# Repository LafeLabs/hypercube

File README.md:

# Geometron Hypercube

## Trash Magic

 Trash Magic self-replicating media which propagates the means of building a civilization entirely from trash and things we can grow.  

## What is the Hypercube?

The Geometron Hypercube is two things: The set of all of the 4 inch cubes we make from cardboard trash which are the basis of our physical technology and a geometric language based on the fundamental symmetries of the Universe.  We construct both of these things in order to make it easier to build Trash Magic, using the power of geometry to build things which can be easily replicated and which can build a very wide range of useful objects.  The word "hypercube" here is used to represent generalizations of the cube into higher dimensions in a broad sense.  We take this to mean a set containing many different cubes of many different kinds.

## The Cardboard Hypercube

The cube is 4 inches on a side and can be used for:

 - pencil/rulers/pens/brushes/shapes box
 - marketing display
 - card box for Geometron Trash Magic Cards
 - mushroom farms
 - worm farms
 - [link to oyster mushroom cardboard farming](https://grocycle.com/grow-mushrooms-on-cardboard/)
 - [buy worms to farm in compost bins](https://unclejimswormfarm.com/order-stuff/composting-worms/)
 - tiny compost piles
 - plants, seedlings
 - dice
 - parts bins
 - motion sense control pyramids
 - motor fixture
 - geometron icon printer tower
 - large collaborative art structures
 - lamps

[tiktok of hand cut cube without a laser](https://www.tiktok.com/t/ZTR8AFMJp)

To make one cube, cut out 12 of these from corrugated cardboard, stack them into four panels 3 layers thick and glue them using Elmer's glue:

.svg file for laser cutter:

Now cut out 3 of the bottom pieces, and stack them into a fifth glued panel. 

.svg file for laser cutter:

Assemble the sides into the base as shown:

Cut out 4 inch squares, print on them, glue them to the panels, and hold it all together with rubber bands:

Every cube we produce in the Trash Robot Network is part of the Geometron Hypercube.  Therefore to grow the Hypercube, we produce and distribute as many cubes as we can, and always evolve the cubes to make them better over time and to solve specific problems to bring us closer to Trash Magic.

## Action Geometry Tools: Rulers and Shapes

To make geometric constructions out of cardboard trash, we use the tools of Action Geometry, which are created with the Geometron Language.  These include the ruler, which we cut from 0.2 or 0.25 inch thick neon green acrylic and the shape sets which we cut from 0.1 or 0.125 inch thick neon green acrylic.  

### Geometron Ruler

The Geometron Ruler is one inch by six inches. One side has tenths and the other halves, quarters and eights. The highest quality rulers are made from quarter inch neon green acrylic with a laser cutter.  Any ruler can be used to make more rulers.  Cereal box cardboard is a good material.  Find a maker space or individual with a laser cutter.  Dig through the waste bin to find extra acrylic.  Place the outlines and etch and make rulers.  Give them away and spread the word of Geometron, Trash Magic, Trash Robot and so on.  Also you can use [Ponoko.com](https://www.ponoko.com/) to get large numbers of rulers made and can sell those if you so choose.  

Using Ponoko.com is only cost effective if you have a budget of over 1000 dollars, then the cost per ruler can drop to about a dollar and a half.  Also, Ponoko only has eighth inch acrylic and quarter inch is the nicest.  For best results, go find 0.2 inch or quarter inch neon green acrylic somewhere, find a laser cutter and print these out yourself.  All the files for this are below.  

This is some 6 inch rulers from both green and yellow acrylic and a 15 cm metric ruler.

Ruler Outline SVG file:

Ruler Etch pattern PNG file:  

Ruler 2 color SVG file for Ponoko.com:

Set of 8 rulers in one SVG file for Ponoko.com:

Centimeters PNG file for etch.  Print out with 15 centimeter width and 2 cm height:

centimeters Ruler Outline SVG file, line up with etch and make 15x2 cm:

One ruler with etch and cut in different layers:

Set of 8 cm rulers in one SVG file for Ponoko.com:

## Shapes

These shapes are used for constructions based on fundamental symmetries: fourfold, eightfold, threefold, fivefold, and sixfold.  For best results, we cut them out from eight inch neon green acrylic with a laser cutter.

.svg file for use in laser cutter.  Each shape has side of 3 inches, so this is a 6 inch wide file:

These can all also be constructed using the tools of classical geometry(compass and ruler) or a ruler and a protractor.  So they can be made by hand and cut out from cardboard or paper trash if no laser or acrylic is available.

##  Geometron Icon Printer
 
 - [link to program the Arduino UNO in the Printer Robot](arduino.html)
 - [link to global image feed](globalimagefeed.html)
 - [link to image aligner](alignimage.html)
 - [link to icon tracer](traceicon.html)
 - [link to icon set](iconset.html)

## Things to buy for the electronics kit:

 - [3 motor controller boards from Pololu(10x3=$30)](https://www.pololu.com/product/2966)
 - [Custom printed circuit board to connect Arduino to controllers and connectors($2/ea in lots of 20 with shipping)](https://www.pcbway.com/project/shareproject/Trash_Robot_main__brain__board.html)
 - [straight 0.1 inch headers from Digikey(buy about 2 per kit at about 60 cents each)](https://www.digikey.com/en/products/detail/chip-quik-inc/HDR100IMP40M-G-V-TH/5978197)
 - [Ribbon cable from Digikey(about $8 for about 6 kits worth for about $2/kit rounding up )](https://www.digikey.com/en/products/detail/assmann-wsw-components/AWG28-20-F-1-300-R/2391636)
 - [8 buttons for controller from Digikey(about $1 for all 8)](https://www.digikey.com/en/products/detail/te-connectivity-alcoswitch-switches/FSM2JRT/529664)
 - [Cables from Digikey to connect stepper motors in DVD drive stages to circuit board(about $10 for 3 of them)](https://www.digikey.com/en/products/detail/molex/2177971043/14637940)
 - [Arduino Uno from Sparkfun($25, some off brand UNOs have power supply problems for this application, test any new board to see if it stalls out)](https://www.sparkfun.com/products/11021)
 - [9 pin socket headers](https://www.digikey.com/en/products/detail/samtec-inc/SSQ-109-03-T-S/1111949)

## Kit Photo:

## Control Panel Geometry

## Assembled Electronics Kit Photo

##  DVD drive cables

[Cables from Digikey to connect stepper motors in DVD drive stages to circuit board(about $10 for 3 of them)](https://www.digikey.com/en/products/detail/molex/2177971043/14637940)

## Z axis Stage Assembly

## X and Y axis stage assemblies

## Sproing

Two each of a 0.5 inch by 4 inch thin HDPE sheet and two 0.5 inches by 3 inches thick stiffer plastic.  All held on by rubber bands as shown, as well as attached to the Z stage.

## Full assembly

[link to icon design scroll](scrolls/icons)

[link back to home scroll](scrolls/home)

## Arduino Shields

 - hole in the bottom of box image with ruler position
 - eagle files
 - link to buy 
 - list of components
 - digikey shopping cart
 - photo of assembly for neopixel
 - photo of assembly for sense pyramid
 - sense pyramid photo
 - sense pyramid triangles
 - link to neopixel code
 - link to github repo
 - link to pyramids 3 sense code
 - photo of rotor setup

## Card Magic

## Bags and Flags

## Hypercube Cart

 - 200 W solar panel
 - lead acid battery power plant with weather protection
 - 12x8 inch laser cutter with 40 or 50 W CO2 laser, converted to geometron operation
 - independent suspension and weather protection for laser cutter
 - power output: 12 volt regulated, USB chargers, inverter for AC wall power
 - power input: solar panels, wall charge, car charge, bicycle charger, wind, water
 - Raspberry Pi Geometron Server with the whole system from [https://github.com/LafeLabs/hypercube](https://github.com/LafeLabs/hypercube)
 - setup for pi with small screen, projector, portable screen for projector, geometron keyboard(s), mouse, USB thumb drive to get files onto pi crust
 - neopixel strips lighting up the whole system
 - arduino shields for neopixel, pyramids, motors, robots, etc, arduino setups, boards
 - cube stack: lots of cubes of all kinds: card boxes, art boxes, parts boxes, planters with plants, fungi, compost, empties, parts to make more
 - fully set up geometron icon printer to print on cards, cubes, and trash
 - hanging green wall of plants
 - tarp, awning for getting out of rain 
 - folding chair to sit under awning
 - neon green acrylic shape sets and rulers
 - router to connect to mesh network or cell network and make a wifi hotspot

## Geometron: A Universal Language of Geometric Construction

Geometron is a language for creating geometric constructions using these symmetries.  We aim to build the most powerful possible interface between the human mind and the physical world.  To do this we build geometric actions based on the fundamental symmetries of the Universe.  We represent those actions using symbols we construct using that same set of actions.  We describe each of the geometric actions using a human language we understand, with phrases like "draw a unit circle", while also creating symbols which are used in the language to express itself.  

Geometron is constructed independent of any one physical technology to implement it, or any one set of symbols.  It is a means of creating symbolic geometric languages.  The Geometron Hypercube elements which make up the language are an arrangement of geometric actions into cubes.  One cube contains all the actions which are not explicitly symbols, and the other cube represents all the symbols for the actions in the action cube.  Each cube is broken up into a crystal of 8 by 8 by 8 cubes.  Each of those cubes contains a sequence of cube addresses, which are geometric actions.  Thus the Geometron Hypercube is a model for constructing geometric and symbolic languages which we can build up by hand using pencil and paper, and then implement in any computer language relatively quickly.  

A Geometron Glyph is a sequence of these geometric actions which are represented by addresses in the Hypercube.  These glyphs are abstractions which can be expressed as sequences of symbols in any format(a browser, a pen and paper, a printer or plotter) but which can apply to ***any kind of physical construction***.  This might include movements of motors in robotic machines which carry out automation of production, like laser cutters, electron beam writing tools, milling tools or 3d printer heads.  Or it might include lighting up pixels on a screen or deflecting the beam of a cathode ray tube.  

Addresses in the Hypercube all begin with "0" to indicate that they are base 8(digits are all between 0 and 7).  All addresses in the symbol cube have a "1" added.  The Action cube is divided by types of operation into tablets, which are each arrays of 8x8 = 64 actions which can be arranged in a square on a chess board. The planar operations which are used to construct symbols on computers are all in the range from 0300 to 0377(with matching symbols at 01300 to 01377).  The actions in the range from 0200 to 0277(with matching symbols at 01200 to 01277) are all sequences of either planar actions in the 03xy range or other actions in the 02xy range.  Thus we can build up complex structures which call other sub-structures.  This is of critical value for design of technology, as we can create complex systems of systems built up from very simple components in a fractal way.  Addresses in the range from 040 to 0176 correspond to the ASCII codes for the characters which can be printed and have a symbol on standard US keyboards.  Fonts in English are stored as sequences of actions in the range from 01040 to 01176.  The contents of each of the ASCII addresses are actions which are triggered when that key is pressed.  This mapping is what is represented physically in the custom painted Geometron keyboards we build.  

### Geometron Keyboards

We assign keys on physical keyboards to symbols which represent actions in order to make it easier to interact with Geometron on a keyboard.  We make these with paint pens, pain brushes, nail polish, stickers, or any other means of decorating keyboards as follows:

These are edited on a Geometron server using the keyboard editing page linked from the main symbol editor.

### Shape Sets

We can use Geometron to create symbolic languages made up of shapes which can be called using their own symbols.  These can be used to create things like the Action Geometry shapes, electronic schematic diagrams, logic gates, chemical diagrams, architectural diagrams, illustrations, and really any kind of symbolic language including for technology design like circuit layout for fabrication.

Some examples of constructions using shape sets

## Fonts

Fonts correspond to the addresses in the symbol cube which map to the key actions in the action cube. I.e. the address is the ASCII value plus 01000 base 8.

Dot Matrix Font:

Laser cut font:

Katakana dot matrix font:

## Symmetries of the Universe

Symmetries are properties of things which remain the same under geometric transformation.  The Universe as we find it displays certain symmetries again and again in both the living and non living world.  Perhaps the most fundamental of these are crystal lattices, where movement in certain directions by certain distances leads to a repeating of patterns.  Perhaps the next most common symmetries we see in Nature are those of certain special rotations: bilateral symmetry, trilateral symmetry, fourfold, fivefold, sixfold, eightfold, tenfold, and twelvefold.  

Each of these special rotational symmetries has certain scales which are built into them.  When we work with squares and octagons, we find the square root of two and two coming up again and again in 45 degree angle constructions.  When we work with hexagons and equilateral triangles, we get scales by the square root of three, three, and two.  And finally anything with fivefold symmetry has the Golden Ratio built into its construction.  

Movement by one unit, just moving from point to point:

Repeated movements can create crystal lattices, like the checkerboard pattern:

A circle is totally symmetric around rotations:

Bilateral symmetry is particularly common in living things:

Threefold symmetry:

Fourfold symmetry

Fivefold symmetry:

Sixfold symmetry:

Fractal based on triangles:

Fractal based on squares:

Fractal based on hexagons:

Fractal based on hexagons:

Symmetry in Nature:

## Server

The server runs the PI CRUST media network which hosts articles, books, videos, music, podcasts and web pages on local servers over local networks.  We can share books on any format, but there is a native book format for the system called the Pibrary format which is collections of "scrolls" in Markdown format. "Maps" are a sort of generalized meme, layers of images, text and symbols arranged geometrically and with hyperlinks both to other web pages and to other maps on the server.  Maps and Scrolls together can be used to create any kind of static web content we want, and are used for both private web content and for public pages to lead people to the physical media nodes. 

Servers run on a zero security model where there is no private data, no users, no encryption, no property and no commerce or money of any kind.  The *only* information ever put on any server ever is that which we aim to freely share as widely as possible, primarily the means of replication of our system the Hypercube and associated Trash Magic. 

### Install on Pi

Raspberry Pi is now impossible to buy.  Find them donated from someone. Most people who have them don't use them or used them once and stopped due to lack of interest/time/need. Ask around!  Someone will be able to donate a Pi, keyboard, mouse, screen, power supply and whatever other random things you need to get set up.

Get a SD card with 8 GB or more storage and a SD card USB reader

Download and install, then use the Raspberry Pi Imager:

[https://www.raspberrypi.org/software/](https://www.raspberrypi.org/software/)

Turn on the pi click through all the things, put it on the wifi network.

## Install Apache and PHP so that geometron can run

Open a command prompt(black link on menu bar) and type:

```
sudo apt update
sudo apt install apache2 -y
sudo apt install php libapache2-mod-php -y
```

## Install hypercube with this document for self-documentation and replication

```
cd /var/www/html
sudo rm index.html
sudo curl -o replicator.php https://raw.githubusercontent.com/LafeLabs/hypercube/main/php/replicator.txt
cd ..
sudo chmod -R 0777 *
cd html
php replicator.php
sudo chmod -R 0777 *
```

Check the IP address by hovering over the wifi icon, put that into the browser on another machine on the same local wifi network to see and edit the server.  Or open a browser on the pi and point it to [http://localhost](http://localhost)

## Set up to have names for other servers

edit hosts file to have the IP address of the other servers and then the name you want to use, copying the format in the existing file.

```
sudo nano /etc/hosts
```
edit, and use control-x and say "yes" to save changes.

## connect pi to outside internet over router

Look up "set up port forwarding raspberry pi" and follow instructions to log onto your router and forward port 80 to the raspberry pi.  Use [whatismyipaddress.com](https://whatismyipaddress.com/) to get your global IP address.  Now your home Raspberry pi server will be visible on that IP address.  Take that address and make it a link on the remote raspberry pi terminal as well as a QR code on both.   

edit the /etc/hosts file on the remote pi terminal so that home/ and remote/ point to home pi server either on the local network or on the public network.  So "home" will point to the local IP address on the wifi and "remote" will point to the global IP address of the home raspberry pi server(which everyone can see).  

[link to pi my life up](https://pimylifeup.com/raspberry-pi-port-forwarding/)

[link to setting up basic website with pi with external connection](http://unixetc.co.uk/2013/09/21/create-a-basic-website-on-a-raspberry-pi/)

## Install Arduino

the short but not as good way:

```
sudo apt-get install arduino
```

this installs a old version which is missing some features, namely the serial plotter.  following more complicated instructions leads to non-working version which is impossible to uninstall.

how to do the tar ball thing to get a later version of arduino which has the plotting

[https://www.raspberrypi-spy.co.uk/2020/12/install-arduino-ide-on-raspberry-pi/](https://www.raspberrypi-spy.co.uk/2020/12/install-arduino-ide-on-raspberry-pi/)

go get the Arduino software at:

[https://www.arduino.cc/en/software](https://www.arduino.cc/en/software)

and download "Linux ARM 32 bits".

Open a terminal and go to the home directory:

```
cd ~
```

Go to downloads folder:
```
cd Downloads
```
list the files with 
```
ls
```
See the name of an archive with a name like "arduino-####-linuxarm.tar.xz", where #### is a version number.

extract with 
```
tar -xf arduino-####-linuxarm.tar.xz
```

move the extracted information to opt directory(directory for package installation)

```
sudo mv arduino-#### /opt
```

then run the install script:
```
sudo /opt/arduino-####/install.sh
```

## Add python that we need for doing science

[https://matplotlib.org/](https://matplotlib.org/)

matplotlib install:

```
sudo apt install python3-matplotlib
```

[https://matplotlib.org/](https://matplotlib.org/)

[https://www.instructables.com/Jupyter-Notebook-on-Raspberry-Pi/](https://www.instructables.com/Jupyter-Notebook-on-Raspberry-Pi/)

```
sudo apt-get update
sudo apt-get install python3-scipy
sudo pip3 install --upgrade pip
reboot
sudo pip3 install jupyter
```

### Install on Windows or Mac

First, install XAMPP, a free open source web server for all platforms.  [Download from www.apachefriends.org](https://www.apachefriends.org/index.html).  Click on windows to download, and click through to install everything.

After you download and install it, run it and start Apache.  You should see a control panel like this:

Click on "Explorer" to get access to where the files are.  From the main directory called xamp, you want the sub-directory "htdocs".  Open this, delete the index.php file, and create a new file called replicator.php which you copy and paste the replicator at [php/replicator.txt](php/replicator.txt) into, and save.  

Point a web browser on the same computer to [http://localhost/](http://localhost), then click on replicator.php.  This should replicate the whole system into the directory.  When this is done, click the link to go to the main page.  

### Install on Android

To run a Geometron Server on an Android, we will install the commercial software ksweb pro.

[link to play store to install ksweb](https://www.google.com/url?sa=t&rct=j&q=&esrc=s&source=web&cd=&cad=rja&uact=8&ved=2ahUKEwiLrtjPw6fxAhUQu54KHWkyAjIQFjAAegQIBRAD&url=https%3A%2F%2Fplay.google.com%2Fstore%2Fapps%2Fdetails%3Fid%3Dru.kslabs.ksweb%26hl%3Den_US%26gl%3DUS&usg=AOvVaw2ChVP4ojXIuGxVe-JjtEV3)

[https://www.kslabs.ru/](https://www.kslabs.ru/)

Install KSWEB on the Android, and turn it on.  Get the paid version. It is worth it, there are lots of broken web servers out there or ones with crappy features and tons of ads.  This is critical infrastructure for Geometron and it's worth supporting the developer of this useful tool.  Be sure PHP is also turned on.  

This is what it looks like when it is on:

Use the Editor built into the system to create a new file called replicator.php in the directory htdocs on the sd card as shown above, and to copy/paste into that the file in [php/replicator.txt](php/replicator.txt).  Save that, and delete index.php. Point a browser to the address [http://localhost:8080](http://localhost:8080).  Click on replicator.php and wait for the system to copy.  Sometimes it might time out, try it again.  When the system has replicated, make sure your phone is on a local wifi network, and turn the server off and on again, and you will get an IP address for the phone which is shown in the app.  The link for any other machine on the network other than the phone is the IP address followed by colon and then "8080".  E.g. http://192.168.0.19:8080/.  Share this link via email, text message, and links on other servers so that anyone on your network can see your server and edit it.  

### Replicate the Github using localhost

 - install PHP on your machine
 - create a new github repository on a CC0 PUBLIC DOMAIN license and clone it on your machine
 - copy the file [php/replicator.txt](php/replicator.txt) into a file called replicator.php in the new repo directory
 - run `php replicator.php` on your machine, wait for all the code to copy
 - push all that code up to your github repo
 - in the same directory, type `sudo php -S localhost:80`
 - go to [http://localhost](http://localhost) and you should get back to this screen, edit all elements of the system
 - use [editor.php](editor.php) to edit the file php/replicator.txt so that the two urls are the global url for *your* repo for both dna and replicator
 - after you've edited the code, click [text2php.php](text2php.php) to convert that to php
 - push your code to your github repo
 - use the new replicator code on your github repo to replicate out that instance to all other servers(linux, windows, mac, android) and forks
 - when you figure this out, make youtube videos showing other people how to copy the whole system 

## Scroll Sets

## Map Sets

## Pi Crust

## Voxel

 - scroll sets
 - map sets 
 - pi crust 
 - qr code
 - [cube voxel AR memes](voxel.html)

## Trash Robot Bags, Flags and Rags

 - photo of shirts and pants
 - photos of all the bags
 - photos of flags

## Links

 - [copy  trashrobot.html to index.html](copy.php?from=https://raw.githubusercontent.com/LafeLabs/geometronmagic/main/trashrobot.html&to=index.html)
 - [copy latest README.md from github](copy.php?from=https://raw.githubusercontent.com/LafeLabs/geometronmagic/main/README.md&to=README.md)
 - [http://localhost/](http://localhost/)

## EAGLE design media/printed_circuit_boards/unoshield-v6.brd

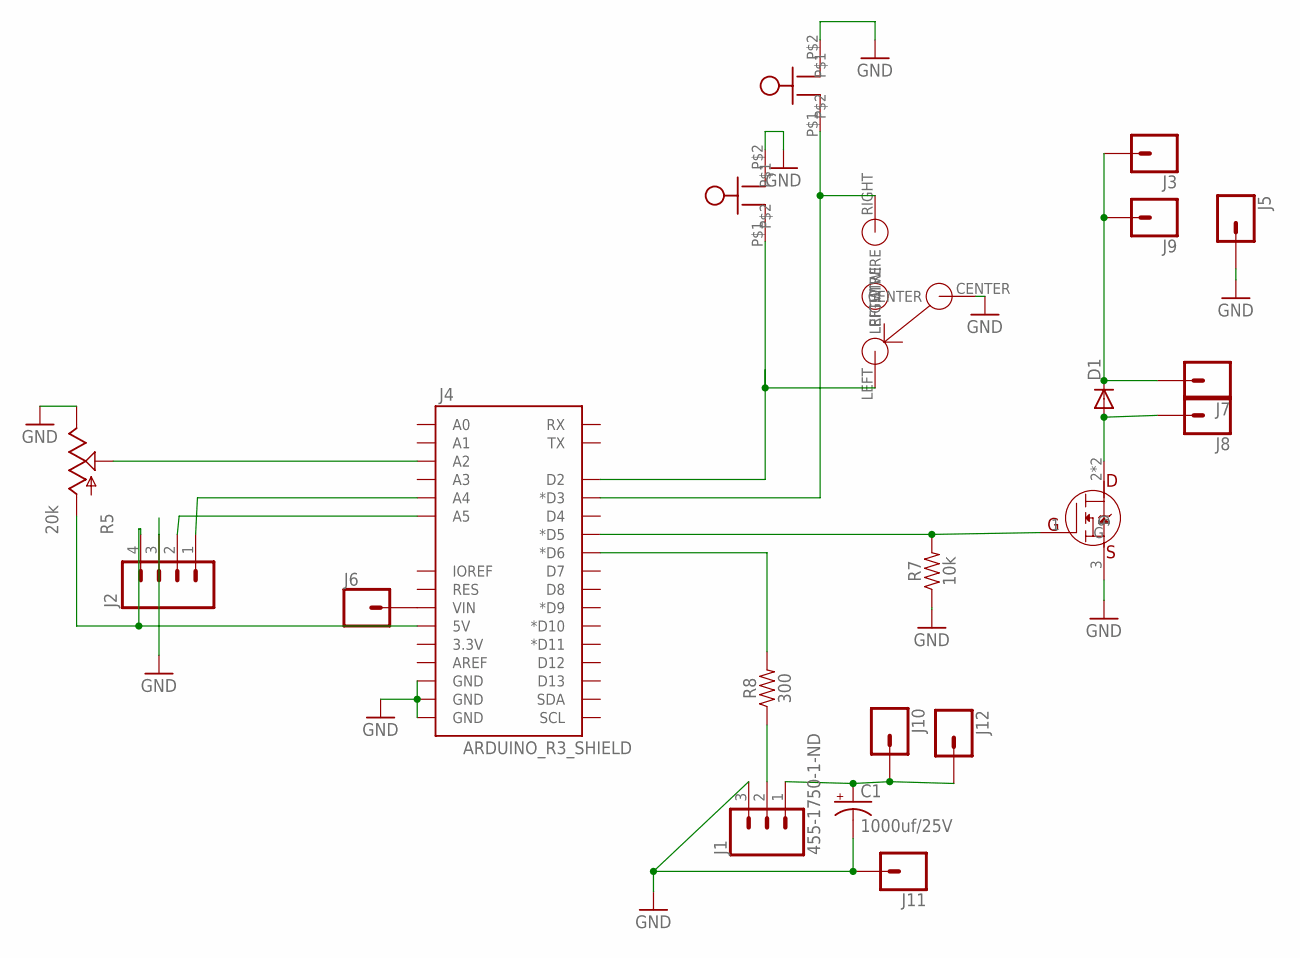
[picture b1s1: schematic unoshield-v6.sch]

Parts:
C1: 1000uf/25V; CPOL-RADIAL-1000UF-25V-KIT
D1: DIODE-DO-214AC; DO-214AC
J1: 455-1750-1-ND; 1X03
J2: M04PTH; 1X04
J3, J5, J7, J8, J10, J11: CONN_01PTH_2MM; 1X01_2MM
J4: ARDUINO_R3_SHIELD; UNO_R3_SHIELD
J6, J9, J12: CONN_01; 1X01
R5: 20k; ALPS_POT_KIT
R7: 10k; AXIAL-0.3
R8: 300; AXIAL-0.3
SW1, SW2: BUTTON
SW3: ON-OFF-ON-360-1013-ND; 360-1013-ND
U$1: IRFL024NPBF; SOT223

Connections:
BUTTON: J4.D3 (*D3), SW2.P$1, SW3.RIGHT (RIGHTWIRE)
CL: J2.2, J4.A5
DA: J2.1, J4.A4
GND: C1.-, J1.3, J2.3, J4.GND@0 (GND), J4.GND@1 (GND), J4.GND@2 (GND), J5.1, J11.1, R5.P$1 (E), R7.P$1 (1), SW1.P$2, SW2.P$2, SW3.CENTER, U$1.3 (S)
unnamed: J4.D5 (*D5), R7.P$2 (2), U$1.1 (G)
unnamed: J4.D6 (*D6), R8.P$2 (2)
unnamed: J4.VIN, J6.1
unnamed: C1.+, J1.1, J10.1, J12.1
unnamed: D1.A, J8.1, U$1.2 (D), U$1.4 (D)
unnamed: J4.D2, SW1.P$1, SW3.LEFT (LEFTWIRE)
unnamed: J1.2, R8.P$1 (1)
unnamed: J4.A2, R5.P$2 (S)
VCC: J2.4, J4.5V, R5.P$3 (A)
VIN: D1.C, J3.1, J7.1, J9.1

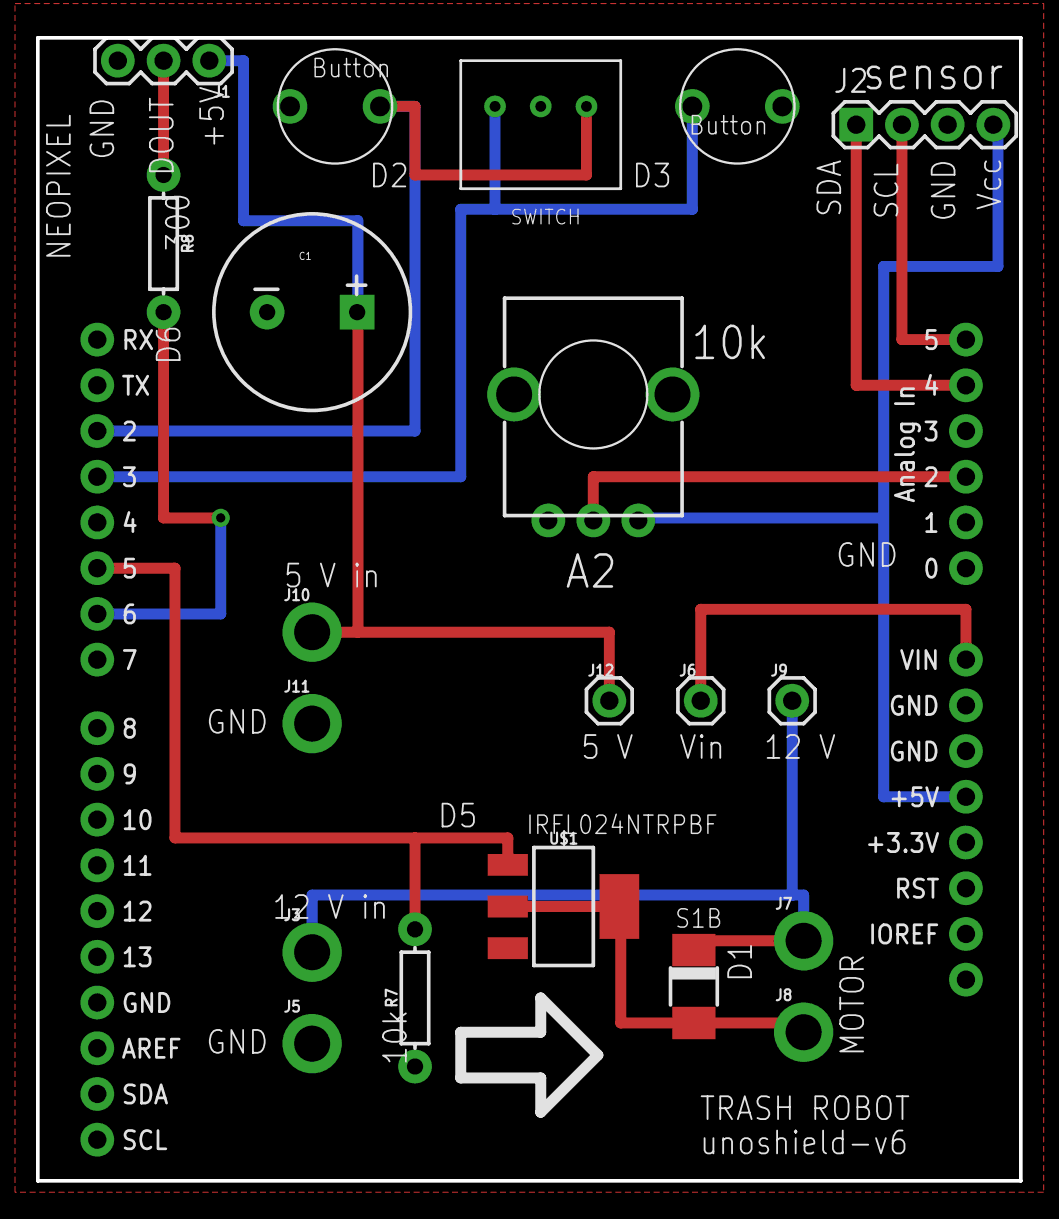
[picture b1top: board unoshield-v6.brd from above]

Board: 2 copper layers, 54.6 x 63.5 mm, 21 parts (0 on the bottom side), 14 nets.

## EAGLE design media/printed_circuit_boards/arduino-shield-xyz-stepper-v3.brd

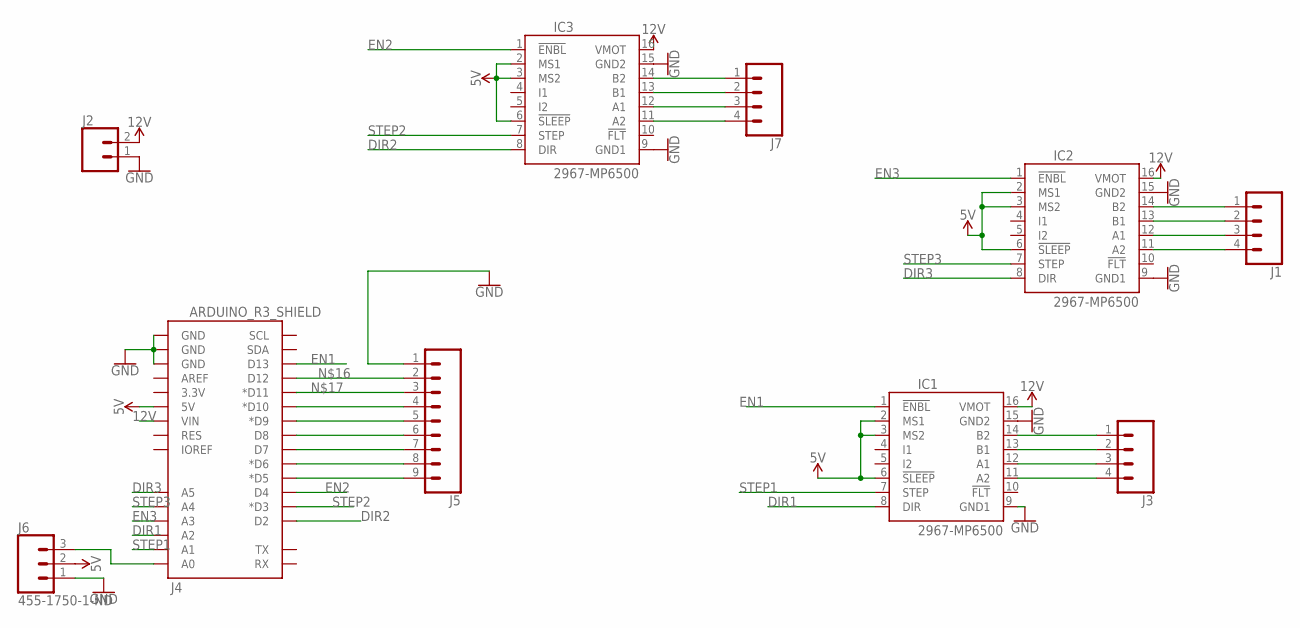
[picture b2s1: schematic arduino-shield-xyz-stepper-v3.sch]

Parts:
IC1, IC2, IC3: 2967-MP6500; MP6500
J1, J3, J7: CONN_04; 1X04
J2: CONN_02; 1X02
J4: ARDUINO_R3_SHIELD; UNO_R3_SHIELD
J5: CONN_09; 1X09
J6: 455-1750-1-ND; 1X03

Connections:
5V: IC1.2 (MS1), IC1.3 (MS2), IC1.6 (!SLEEP), IC2.2 (MS1), IC2.3 (MS2), IC2.6 (!SLEEP), IC3.2 (MS1), IC3.3 (MS2), IC3.6 (!SLEEP), J4.5V, J6.2
12V: IC1.16 (VMOT), IC2.16 (VMOT), IC3.16 (VMOT), J2.2, J4.VIN
DIR1: IC1.8 (DIR), J4.A2
DIR2: IC3.8 (DIR), J4.D2
DIR3: IC2.8 (DIR), J4.A5
EN1: IC1.1 (!ENBL), J4.D13
EN2: IC3.1 (!ENBL), J4.D4
EN3: IC2.1 (!ENBL), J4.A3
GND: IC1.9 (GND1), IC1.15 (GND2), IC2.9 (GND1), IC2.15 (GND2), IC3.9 (GND1), IC3.15 (GND2), J2.1, J4.GND@0 (GND), J4.GND@1 (GND), J4.GND@2 (GND), J5.1, J6.1
unnamed: IC3.14 (B2), J7.1
unnamed: IC3.13 (B1), J7.2
unnamed: IC1.14 (B2), J3.1
unnamed: IC1.13 (B1), J3.2
unnamed: IC1.12 (A1), J3.3
unnamed: IC1.11 (A2), J3.4
unnamed: IC2.14 (B2), J1.1
unnamed: IC2.13 (B1), J1.2
unnamed: IC2.12 (A1), J1.3
unnamed: IC2.11 (A2), J1.4
unnamed: IC3.12 (A1), J7.3
unnamed: IC3.11 (A2), J7.4
unnamed: J4.A0, J6.3
unnamed: J4.D12, J5.2
unnamed: J4.D11 (*D11), J5.3
unnamed: J4.D10 (*D10), J5.4
unnamed: J4.D9 (*D9), J5.5
unnamed: J4.D8, J5.6
unnamed: J4.D7, J5.7
unnamed: J4.D6 (*D6), J5.8
unnamed: J4.D5 (*D5), J5.9
STEP1: IC1.7 (STEP), J4.A1
STEP2: IC3.7 (STEP), J4.D3 (*D3)
STEP3: IC2.7 (STEP), J4.A4

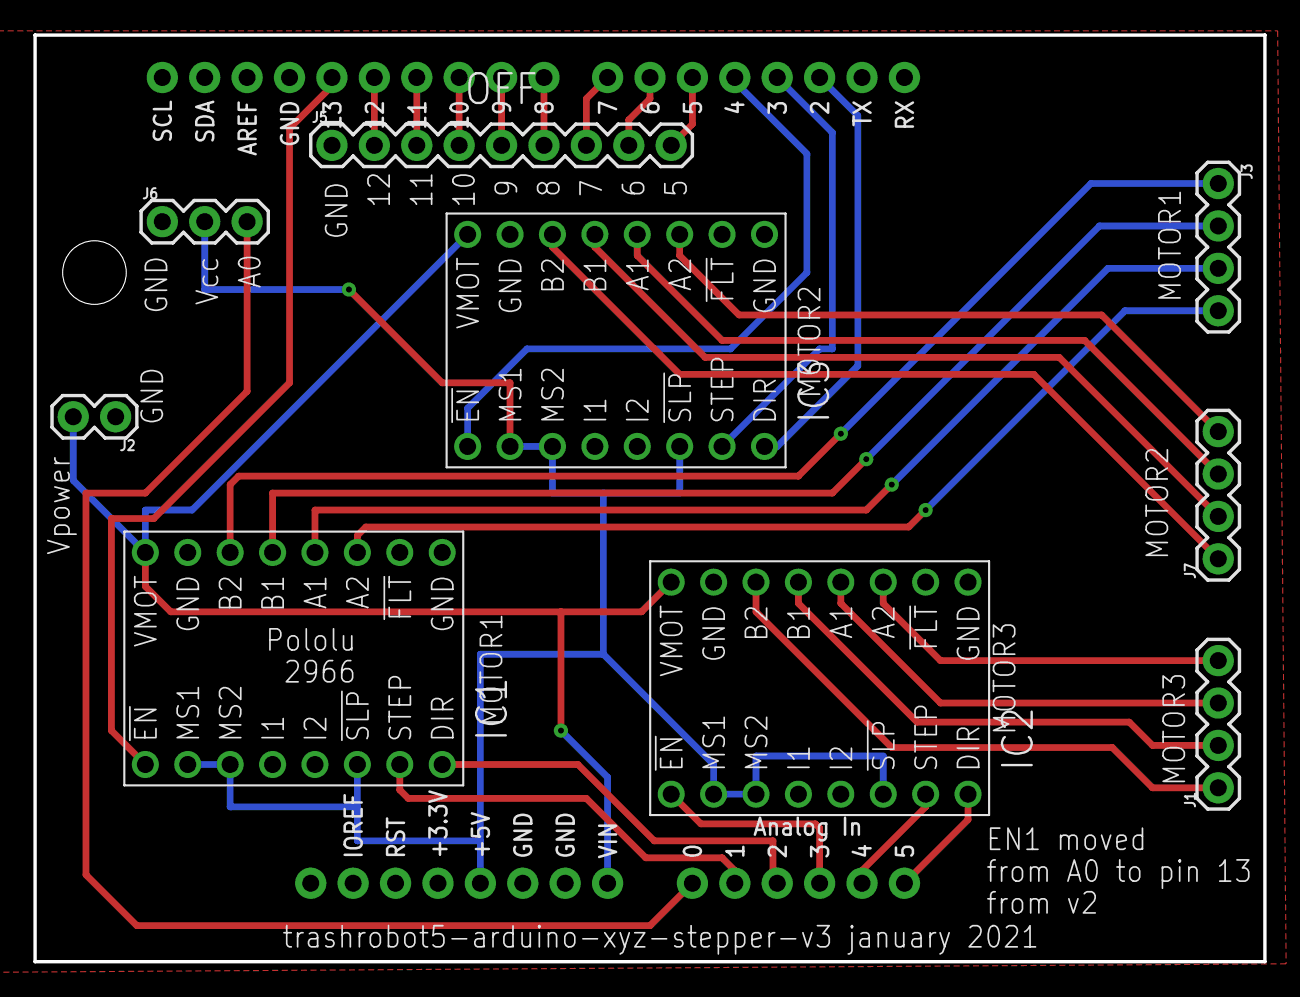
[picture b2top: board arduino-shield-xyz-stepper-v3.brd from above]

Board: 2 copper layers, 73.7 x 55.5 mm, 10 parts (0 on the bottom side), 33 nets.

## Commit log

2022-06-24 hypercube index.html unifies everything
2022-06-24 working on the hypercube page structure
2022-06-24 creating all the sets
2022-06-24 scrolls
2022-06-24 adding things to the feed, adding a public arduino program page
2022-06-24 ui work
2022-06-24 building the scroll set for hypercube
2022-06-24 phone mode css/js
2022-06-24 some nonsense with httpc
2022-06-24 uploadimages/touchgrass
2022-06-24 photos of cardboard sides
2022-06-24 symbol feed work
2022-06-24 Update home
2022-06-24 Update cubes
2022-06-24 rulerphoto
2022-06-24 ruler
2022-06-24 shapes.jpg
2022-06-24 shapes2.jpg
2022-06-24 scroll work
2022-06-24 controller svg
2022-06-24 more photo documentation
2022-06-24 adding more photos
2022-06-24 sproing.jpg
2022-06-24 scrolls for the printer robot
2022-06-25 various scrolls updates
2022-06-25 scrollset.txt
2022-06-25 picrust
2022-06-25 Update printers
2022-06-25 business
2022-06-25 a couple more scrolls
2022-06-25 just a bit of scroll changes
2022-06-26 dandylion
2022-06-26 working on a geometron scroll
2022-06-26 cube planter photo
2022-06-26 symbols
2022-06-26 reversed direction of x control buttons using pin number assignments
2022-06-28 putting arduino files into the media directory
2022-06-28 fixed backgrounds in fractal diagrams for geometron scroll
2022-06-28 who even knows what i updated this time
2022-06-30 added a trash magic card scroll
2022-07-01 hypercube/cardmagic
2022-07-01 geometron card magic
2022-07-01 Update cards
2022-07-03 added mushroom, worm and seedling to robot feed, added tiktok link in cube scroll
2022-07-03 carts
2022-07-04 put in cube images
2022-07-04 working on readme
2022-07-04 readme work scroll work
2022-07-05 symmetry contemplation scroll
2022-07-05 Update servers
2022-07-05 recursion forever
2022-07-05 fixed symbolset replicator link
2022-07-05 geometornlinks
2022-07-06 Update lasers
2022-07-07 cardmagic, building boards from decks from cards from icons
2022-07-07 cardmaker.html
2022-07-07 card.html
2022-07-07 cardmaker.html is now vastly better
2022-07-07 card scroll points to the apps
2022-07-07 improving card workflow
2022-07-07 card.php
2022-07-07 added arduino programming to cardmaker.html
2022-07-07 adding links to cards
2022-07-08 messing with the links
2022-07-08 made simpler structure of card json
2022-07-08 added a background image and face glyph to cardmaker.html
2022-07-08 updated card.html to have the image and face glyph
2022-07-08 card
2022-07-09 fixing bugs
2022-07-09 added images of cards
2022-07-09 fixed another bug in card.php
2022-07-09 fixing many small things that are annoying
2022-07-09 z index issues with upper left icon are mysterious but kludged
2022-07-10 added space 01040 into arduino encoder
2022-07-10 building card set magic structure
2022-07-11 card creation and destruction work flow and local card hyperlinks
2022-07-12 working with card workflow
2022-07-12 cards now link to scrolls which link back to cards
2022-07-13 card magic
2022-07-13 picrust card
2022-07-14 pi crust work
2022-07-14 picrust work
2022-07-15 adding symbols for panels of the standard cube with symmetries
2022-07-15 added images of cube assembly
2022-07-15 cube replicator image
2022-07-15 recursion on cube
2022-07-15 glue.jpg
2022-07-15 changed key configs in traceicon.html to WASD not ASDF
2022-07-16 webpages.html has link to get back to picrust.html
2022-07-16 scroll replicators pi crust
2022-07-16 recursion recursion recursion
2022-07-16 made a prototype home page in pi crust web for trash robot
2022-07-17 square factory
2022-07-17 symbol feed added to pi crust, removed junk symbols
2022-07-18 internette.html
2022-07-18 iconprinter fork from hypercube
2022-07-18 market.html
2022-07-18 cardmaker now loads card glyphs with a click
2022-07-19 made a picrust fork from hypercube that is just picrust
2022-07-19 hypercube/picrust
2022-07-20 incorporated changes to PI CRUST to hypercube/
2022-07-20 web workflow work
2022-07-20 main hypercube replicator replicates web set now
2022-07-20 little web has all the html files from above as well
2022-07-21 media.html is a thing by itself
2022-07-21 images.html
2022-07-21 images.html and replicator now replicates imagefeed github
2022-07-21 Update replicators
2022-07-21 upload has link to images.html
2022-07-21 iconpage.html makes a page of icons for regular paper printer
2022-07-21 iconpage works but still needs to save .svg
2022-07-21 iconpage.html saves symbolfeed/iconpage.svg, a page of 5x7 icons to print, scale up to full page by hand and print
2022-07-21 better key bindings for tracer, with documentation: wasd and ijkl
2022-07-21 shapes.svg has ruler, 30-60-90 triangle
2022-07-22 images feed is its own thing, deleted some junk
2022-07-22 tweaked unit in shapes.svg to make 1:1 inches on paper printer
2022-07-22 added qrcode for shapes .svg
2022-07-22 trashmagic replicator set card
2022-07-22 trashmagic
2022-07-23 trash magic
2022-07-23 picrust replication
2022-07-23 improving things
2022-07-23 images.html is better
2022-07-25 forked off an icon factory with minimal elements
2022-07-26 made a fork for the website which might or might not get used
2022-07-26 scrollmagic is a thing
2022-07-26 closing some loops on scroll sets
2022-07-27 fork set up
2022-07-27 UI improvement
2022-07-27 trash magic is a magic book from picrust code structure
2022-07-27 trash magic scroll set creation
2022-07-27 filled out the scroll set for trash magic
2022-07-27 trashmagic scroll set might be done
2022-07-28 home scroll update so that hypercube is hypercube, on top of picrust
2022-07-28 better linked lists in scrolls
2022-07-30 tarot.txt icon feed
2022-07-30 working on icon feed replicators
2022-07-30 fork.html link
2022-08-01 image pointing to book geometron magic
2022-08-05 simplecube is a thing
2022-08-05 simplecube
2022-08-07 scroll updates with images of simple cube replicator

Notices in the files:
README.md:
- create a new github repository on a CC0 PUBLIC DOMAIN license and clone it on your machine
parts and their libraries:
SparkFun-Connectors: Licensing: Creative Commons ShareAlike 4.0 International - https://creativecommons.org/licenses/by-sa/4.0
